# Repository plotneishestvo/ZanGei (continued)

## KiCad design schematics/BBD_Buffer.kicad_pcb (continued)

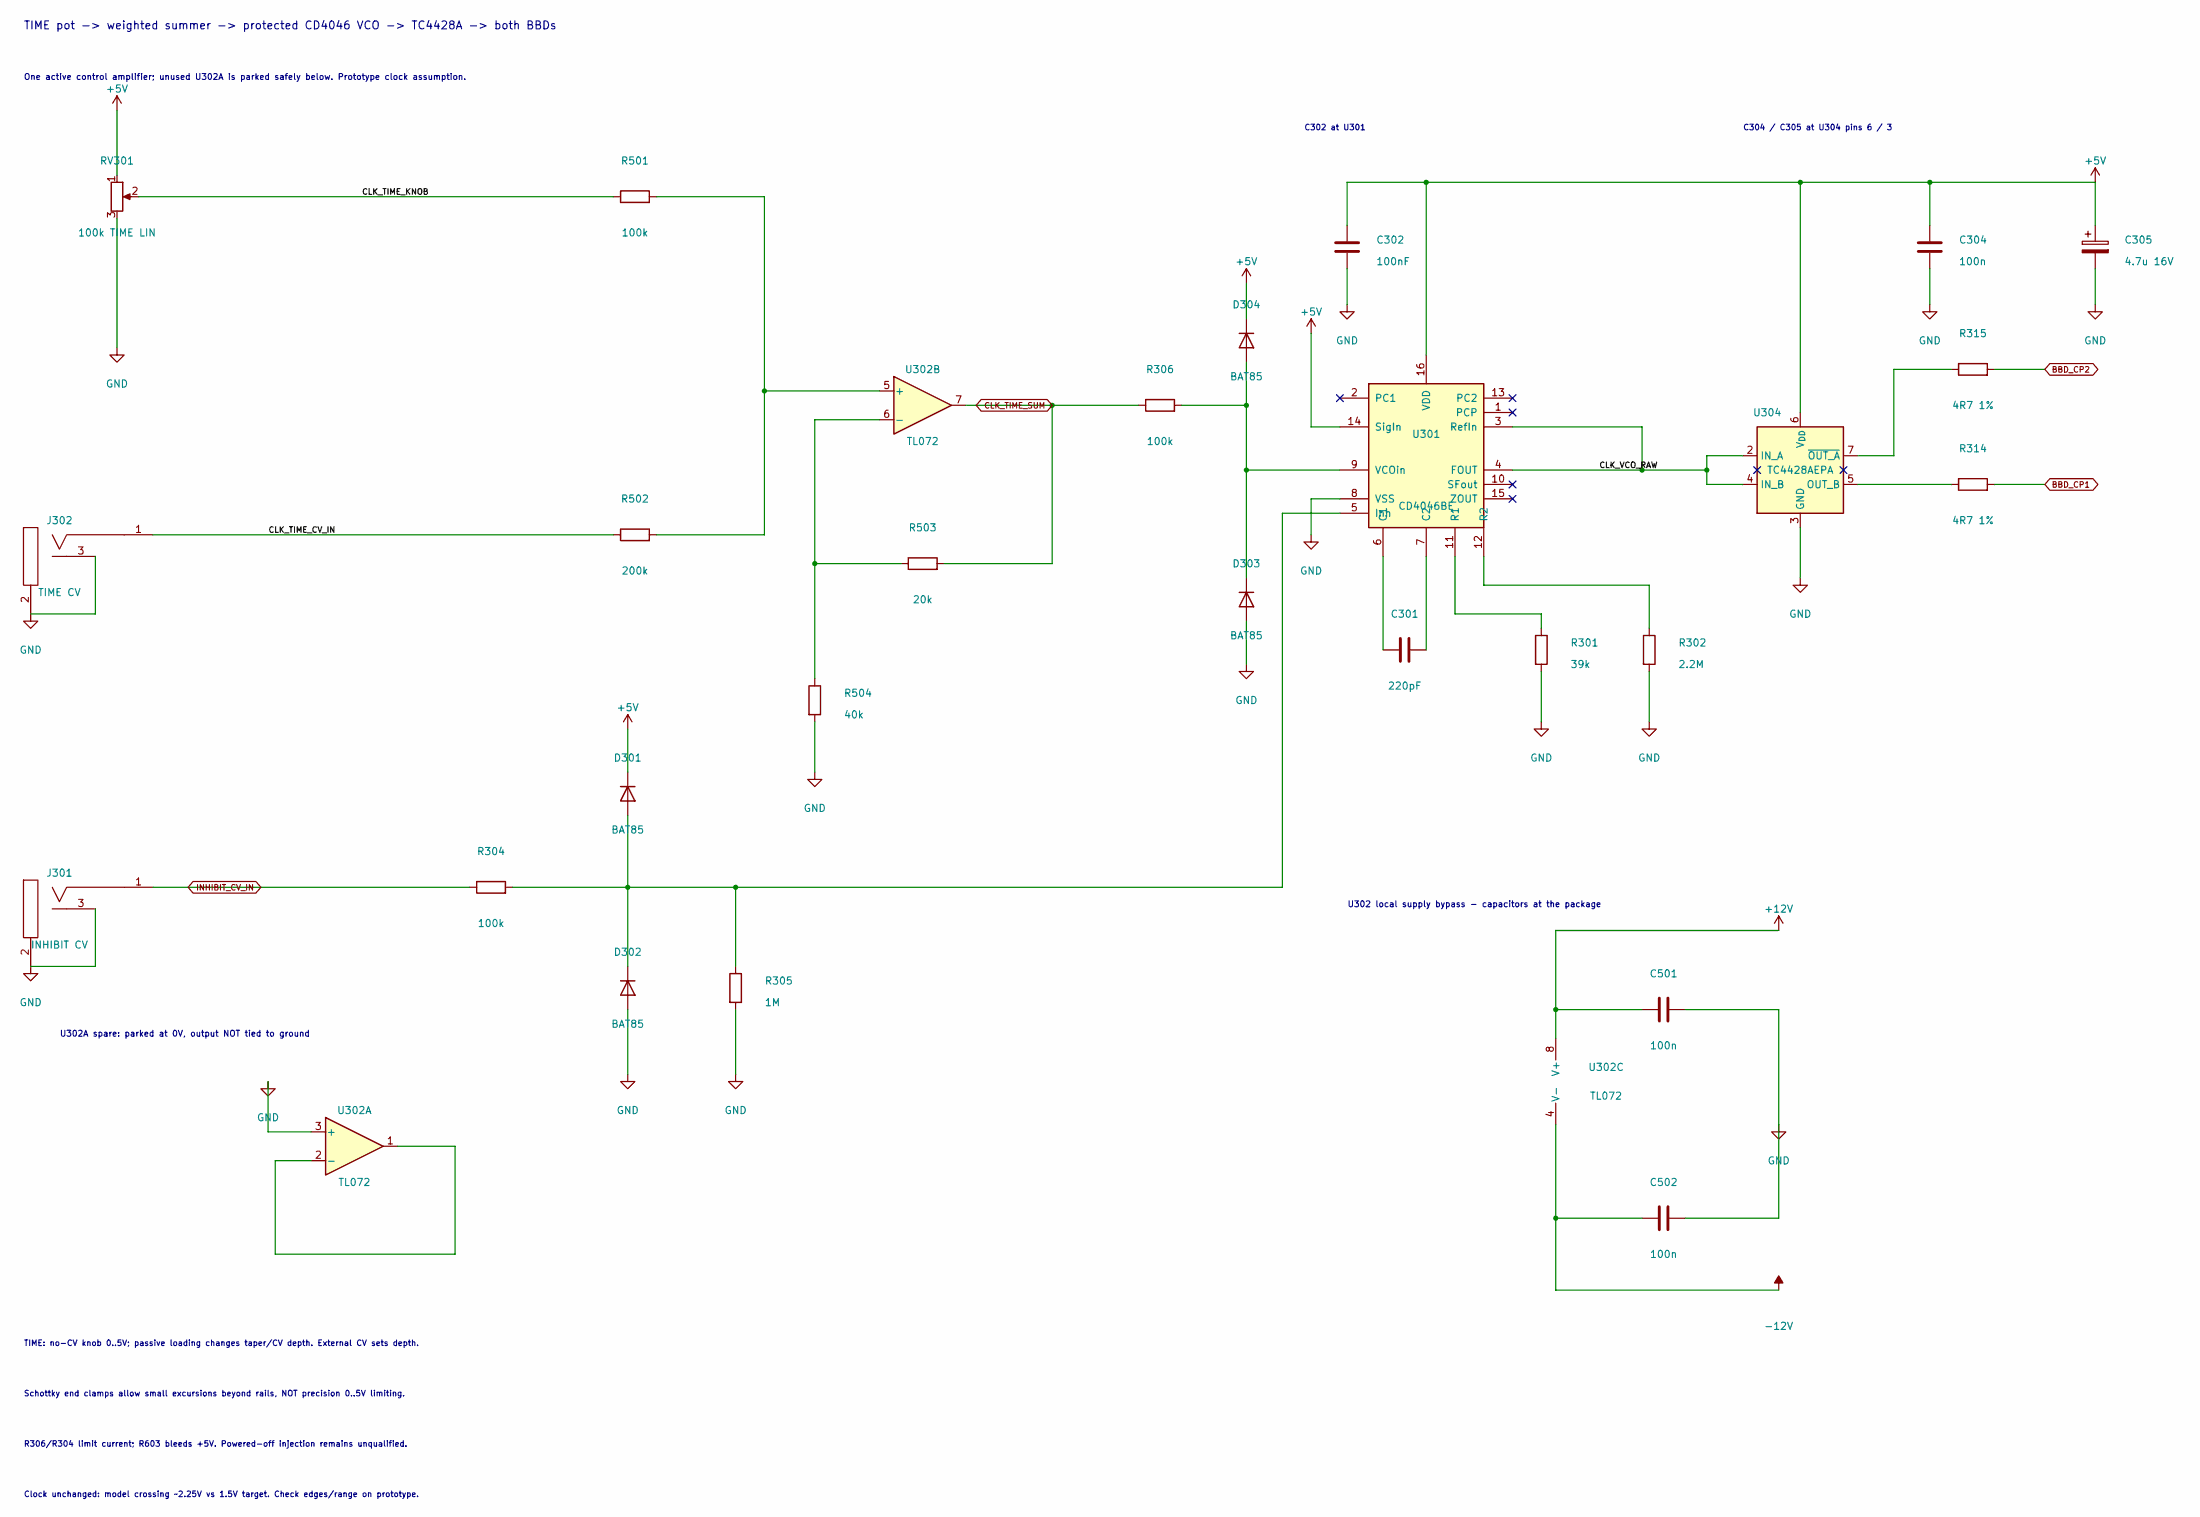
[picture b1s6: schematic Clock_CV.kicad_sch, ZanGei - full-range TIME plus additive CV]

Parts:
C301: 220pF; C_Radial_KEMET_C315_P2.54_Body3.81x5.0
C302: 100nF; C_KEMET_C315C104_P2.54_L3.81_W2.54; MPN C315C104K5R5TA
C304, C501, C502: 100n; C_KEMET_C315C104_P2.54_L3.81_W2.54; MPN C315C104K5R5TA
C305: 4.7u 16V; CP_Radial_D5_H11_P2.00_NoModel
D301, D302, D303, D304: BAT85; D_DO-34_SOD68_P7.62mm_Horizontal
J301: INHIBIT CV; Jack_WQP518MA_PJ398SM_Numeric
J302: TIME CV; Jack_WQP518MA_PJ398SM_Numeric
R301: 39k; R_Axial_L6.8mm_D2.5mm_P10.16mm
R302: 2.2M; R_Axial_L9.25mm_D3.6mm_P12.70mm
R304, R306, R501: 100k; R_Axial_L6.8mm_D2.5mm_P10.16mm
R305: 1M; R_Axial_L6.8mm_D2.5mm_P10.16mm
R314, R315: 4R7 1%; R_Axial_L6.8mm_D2.5mm_P10.16mm
R502: 200k; R_Axial_L6.8mm_D2.5mm_P10.16mm
R503: 20k; R_Axial_L6.8mm_D2.5mm_P10.16mm
R504: 40k; R_Axial_L6.8mm_D2.5mm_P10.16mm
RV301: 100k TIME LIN; Potentiometer_RV09_ExplodingShed_101018
U301: CD4046BE; DIP-16_W7.62mm_Socket
U302: TL072; DIP-8_W7.62mm_Socket
U304: TC4428AEPA; DIP-8_W7.62mm_Socket

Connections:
+5V: C302.1, C304.1, C305.1, D301.1 (K), D304.1 (K), RV301.1, U301.14 (SigIn), U301.16 (VDD), U304.6 (V_{DD}); also elsewhere on the board
+12V: C501.1, U302.8 (V+); also elsewhere on the board
-12V: C502.1, U302.4 (V-); also elsewhere on the board
/Clock and CV/CLK_TIME_CV_IN: J302.1 (SIG), R502.1
/Clock and CV/CLK_TIME_KNOB: R501.1, RV301.2
/Clock and CV/CLK_VCO_RAW: U301.3 (RefIn), U301.4 (FOUT), U304.2 (IN_A), U304.4 (IN_B)
BBD_CP1: R314.2; also elsewhere on the board
BBD_CP2: R315.2; also elsewhere on the board
CLK_TIME_SUM: R306.1, R503.2, U302.7; also elsewhere on the board
GND: C302.2, C304.2, C305.2, C501.2, C502.2, D302.2 (A), D303.2 (A), J301.2 (SHEILD), J301.3 (SW), J302.2 (SHEILD), J302.3 (SW), R301.2, R302.2, R305.2, R504.2, RV301.3, U301.8 (VSS), U302.3 (+), U304.3 (GND); also elsewhere on the board
INHIBIT_CV_IN: J301.1 (SIG), R304.1; also elsewhere on the board
unnamed: D301.2 (A), D302.1 (K), R304.2, R305.1, U301.5 (Inh)
unnamed: D303.1 (K), D304.2 (A), R306.2, U301.9 (VCOin)
unnamed: C301.1, U301.6 (C1)
unnamed: C301.2, U301.7 (C2)
unnamed: R301.1, U301.11 (R1)
unnamed: R302.1, U301.12 (R2)
unnamed: U302.1, U302.2 (-)
unnamed: R501.2, R502.2, U302.5 (+)
unnamed: R503.1, R504.1, U302.6 (-)
unnamed: R314.1, U304.5 (OUT_B)
unnamed: R315.1, U304.7 (~OUT_A)

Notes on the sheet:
Clock unchanged: model crossing ~2.25V vs 1.5V target. Check edges/range on prototype.
U302A spare: parked at 0V, output NOT tied to ground
R306/R304 limit current; R603 bleeds +5V. Powered-off injection remains unqualified.
TIME: no-CV knob 0..5V; passive loading changes taper/CV depth. External CV sets depth.
TIME pot -> weighted summer -> protected CD4046 VCO -> TC4428A -> both BBDs
C304 / C305 at U304 pins 6 / 3
One active control amplifier; unused U302A is parked safely below. Prototype clock assumption.
U302 local supply bypass - capacitors at the package
C302 at U301
Schottky end clamps allow small excursions beyond rails, NOT precision 0..5V limiting.

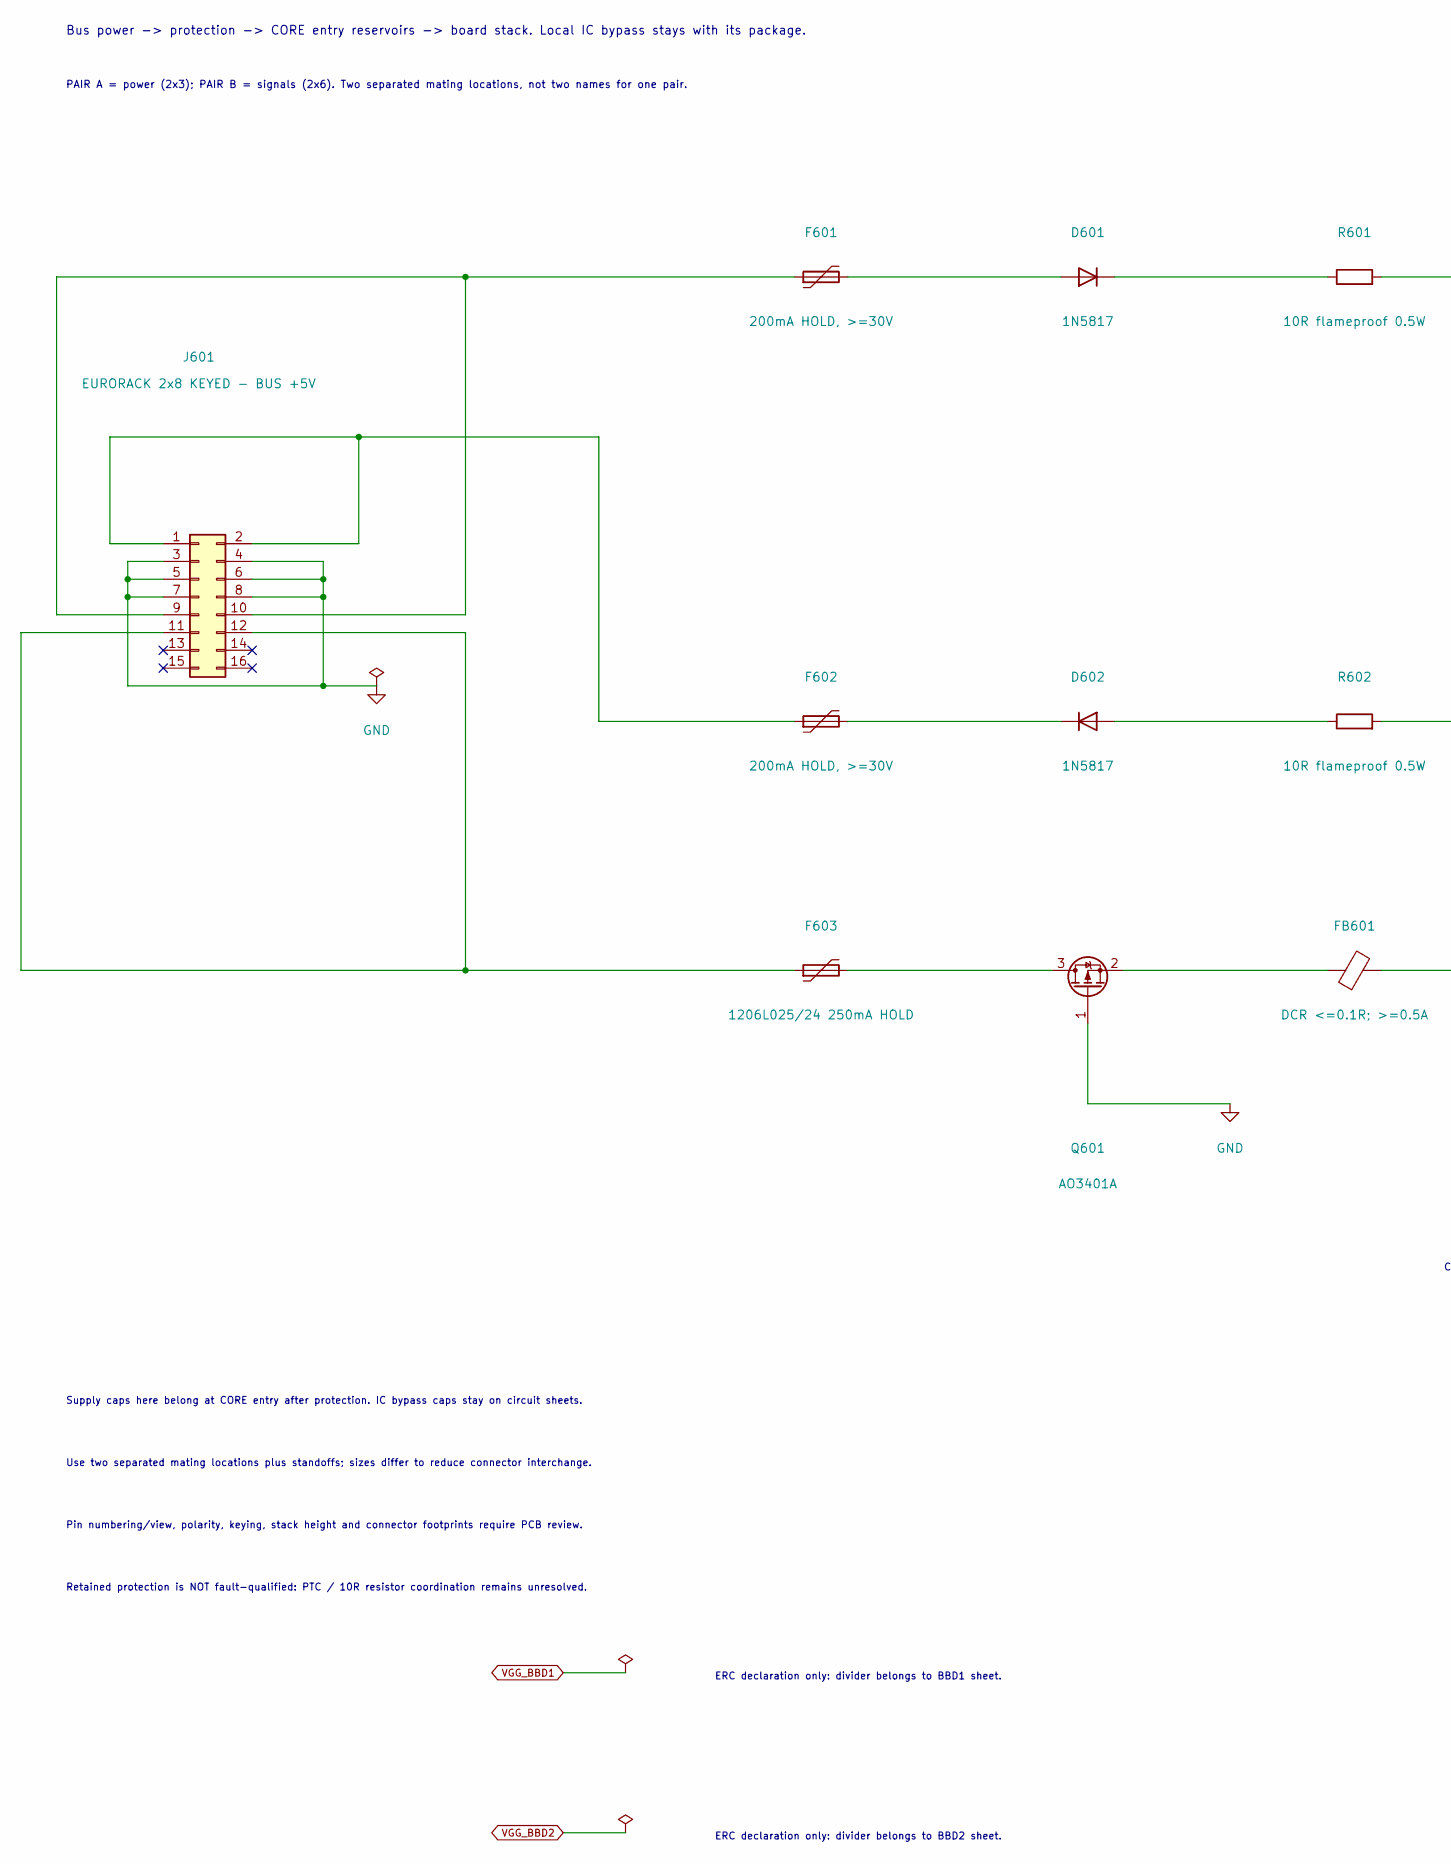
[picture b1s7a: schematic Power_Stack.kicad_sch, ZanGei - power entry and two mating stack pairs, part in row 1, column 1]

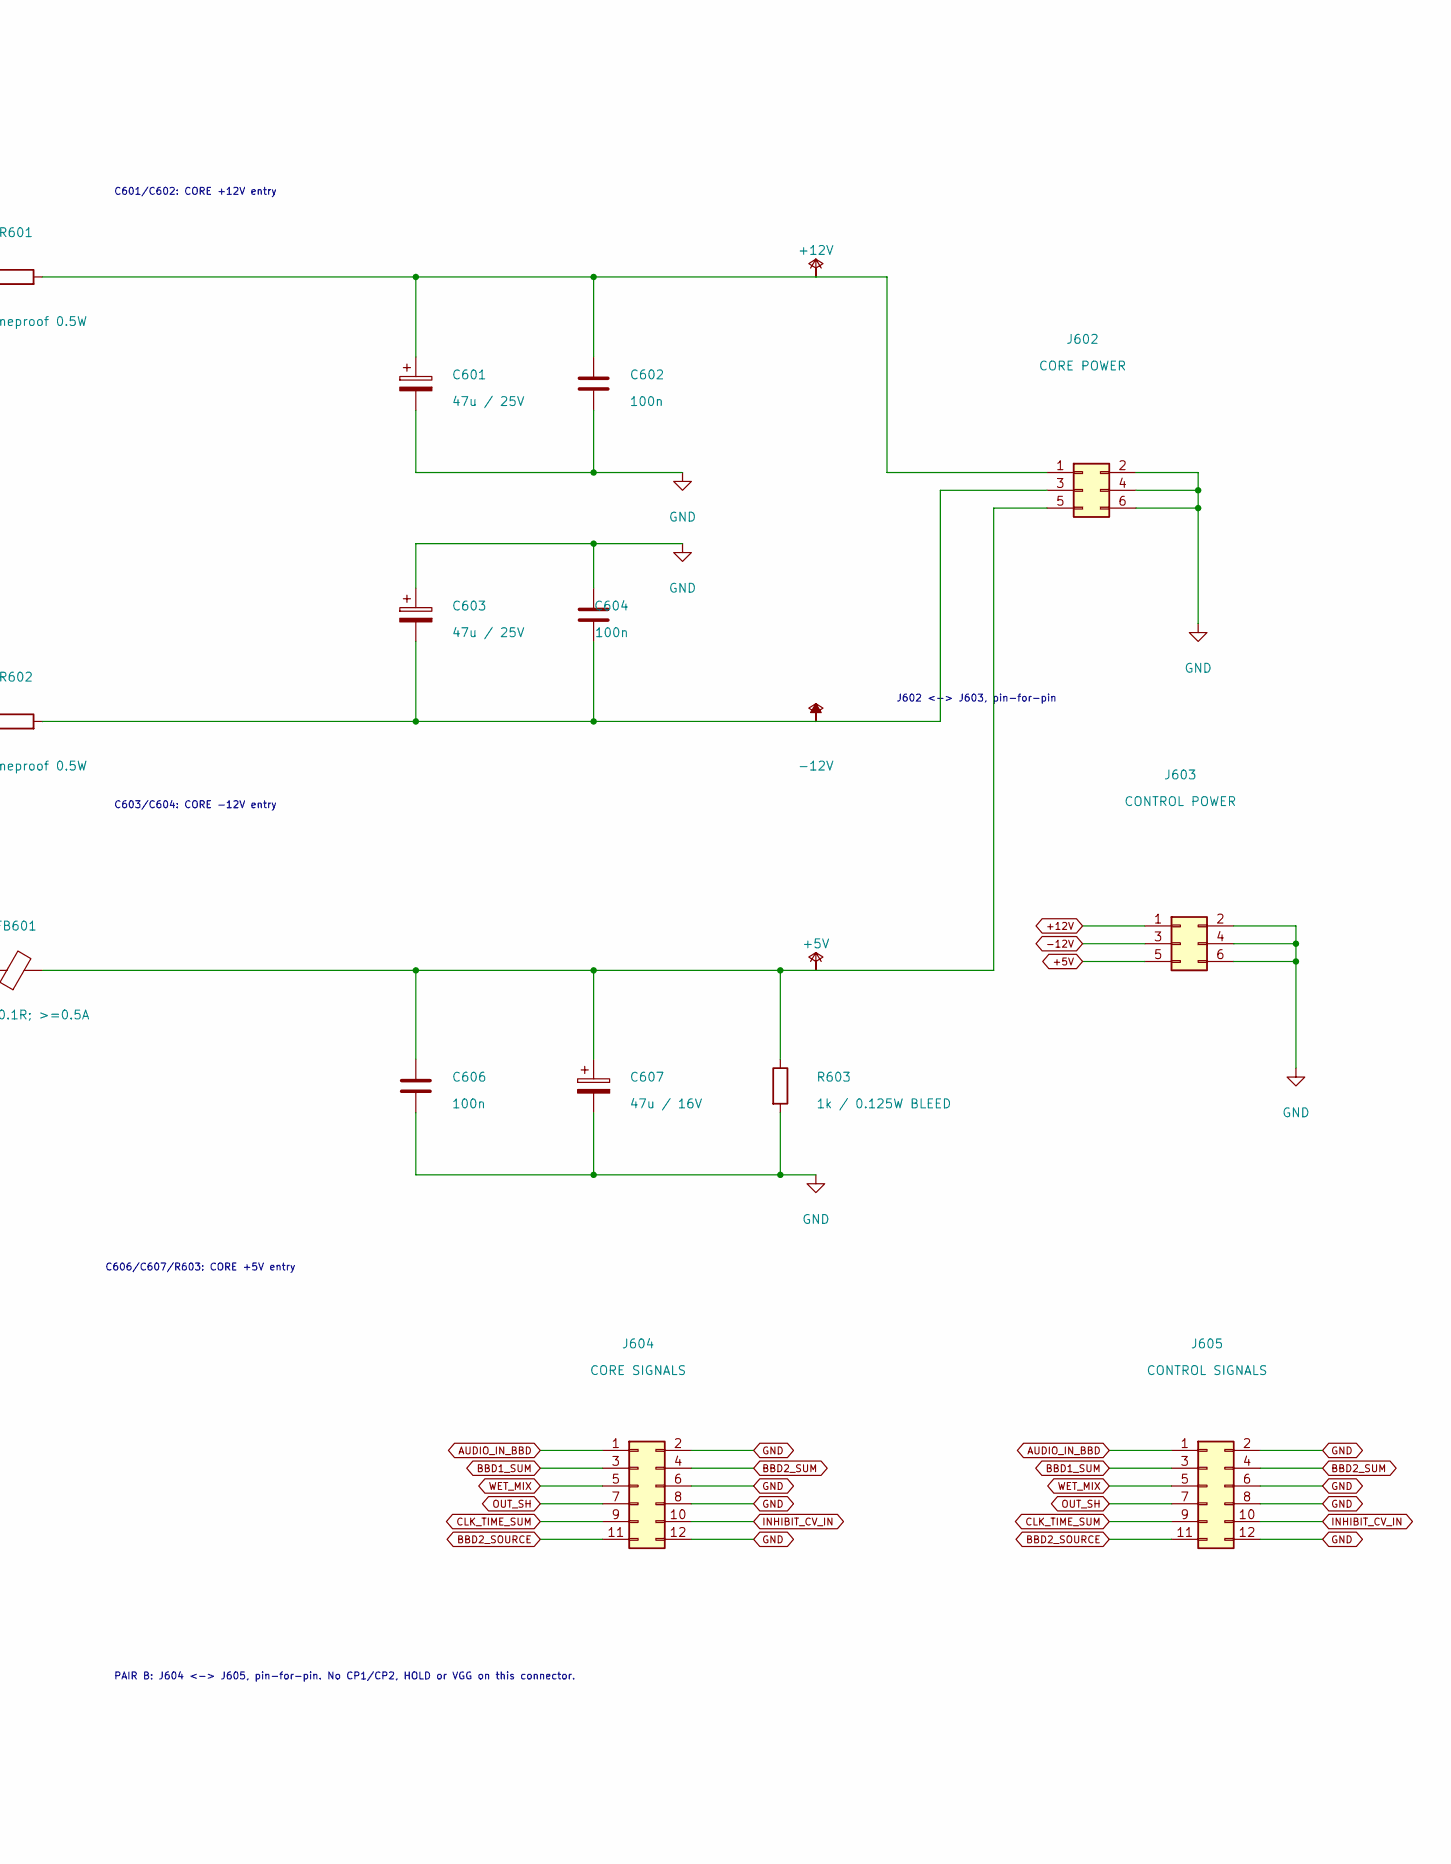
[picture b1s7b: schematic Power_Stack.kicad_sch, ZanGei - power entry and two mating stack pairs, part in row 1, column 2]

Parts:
C601, C603: 47u / 25V; CP_Radial_D6.3mm_P2.50mm
C602, C604, C606: 100n; C_KEMET_C315C104_P2.54_L3.81_W2.54; MPN C315C104K5R5TA
C607: 47u / 16V; CP_Radial_D6.3mm_P2.50mm
D601, D602: 1N5817; D_DO-41_SOD81_P10.16mm_Horizontal
F601, F602: 200mA HOLD, >=30V; PTC_Bourns_MF-R020_P5.10; MPN MF-R020-2
F603: 1206L025/24 250mA HOLD; PTC_Littelfuse_1206L_ManufacturerLands; MPN 1206L025/24YR
FB601: DCR <=0.1R; >=0.5A; Ferrite_Murata_BLM31PG_Pads1.5x1.8_Gap2.0; MPN BLM31PG121SN1L
J601: EURORACK 2x8 KEYED - BUS +5V; IDC-Header_2x08_P2.54mm_Vertical
J602: CORE POWER; PinHeader_2x03_P2.54mm_Vertical
J603: CONTROL POWER; PinSocket_2x03_P2.54mm_Vertical
J604: CORE SIGNALS; PinHeader_2x06_P2.54mm_Vertical
J605: CONTROL SIGNALS; PinSocket_2x06_P2.54mm_Vertical
Q601: AO3401A; SOT-23-3
R601, R602: 10R flameproof 0.5W; R_Axial_L6.8mm_D2.5mm_P10.16mm; MPN NFR25H0001009JR500
R603: 1k / 0.125W BLEED; R_Axial_L6.8mm_D2.5mm_P10.16mm

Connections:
+5V: C606.1, C607.1, FB601.2, J602.5, J603.5, R603.1; also elsewhere on the board
+12V: C601.1, C602.1, J602.1, J603.1, R601.2; also elsewhere on the board
-12V: C603.2, C604.1, J602.3, J603.3, R602.2; also elsewhere on the board
AUDIO_IN_BBD: J604.1, J605.1; also elsewhere on the board
BBD1_SUM: J604.3, J605.3; also elsewhere on the board
BBD2_SOURCE: J604.11, J605.11; also elsewhere on the board
BBD2_SUM: J604.4, J605.4; also elsewhere on the board
CLK_TIME_SUM: J604.9, J605.9; also elsewhere on the board
GND: C601.2, C602.2, C603.1, C604.2, C606.2, C607.2, J601.3, J601.4, J601.5, J601.6, J601.7, J601.8, J602.2, J602.4, J602.6, J603.2, J603.4, J603.6, J604.2, J604.6, J604.8, J604.12, J605.2, J605.6, J605.8, J605.12, Q601.1 (G), R603.2; also elsewhere on the board
INHIBIT_CV_IN: J604.10, J605.10; also elsewhere on the board
unnamed: D601.2 (A), F601.2
unnamed: D601.1 (K), R601.1
unnamed: D602.2 (A), R602.1
unnamed: D602.1 (K), F602.2
unnamed: F602.1, J601.1, J601.2
unnamed: F601.1, J601.9, J601.10
unnamed: F603.1, J601.11, J601.12
unnamed: F603.2, Q601.3 (D)
unnamed: FB601.1, Q601.2 (S)
OUT_SH: J604.7, J605.7; also elsewhere on the board
WET_MIX: J604.5, J605.5; also elsewhere on the board

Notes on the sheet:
Pin numbering/view, polarity, keying, stack height and connector footprints require PCB review.
C606/C607/R603: CORE +5V entry
ERC declaration only: divider belongs to BBD1 sheet.
Supply caps here belong at CORE entry after protection. IC bypass caps stay on circuit sheets.
PAIR B: J604 <-> J605, pin-for-pin. No CP1/CP2, HOLD or VGG on this connector.
PAIR A = power (2x3); PAIR B = signals (2x6). Two separated mating locations, not two names for one pair.
ERC declaration only: divider belongs to BBD2 sheet.
J602 <-> J603, pin-for-pin
Retained protection is NOT fault-qualified: PTC / 10R resistor coordination remains unresolved.
C601/C602: CORE +12V entry
C603/C604: CORE -12V entry
Use two separated mating locations plus standoffs; sizes differ to reduce connector interchange.
Bus power -> protection -> CORE entry reservoirs -> board stack. Local IC bypass stays with its package.

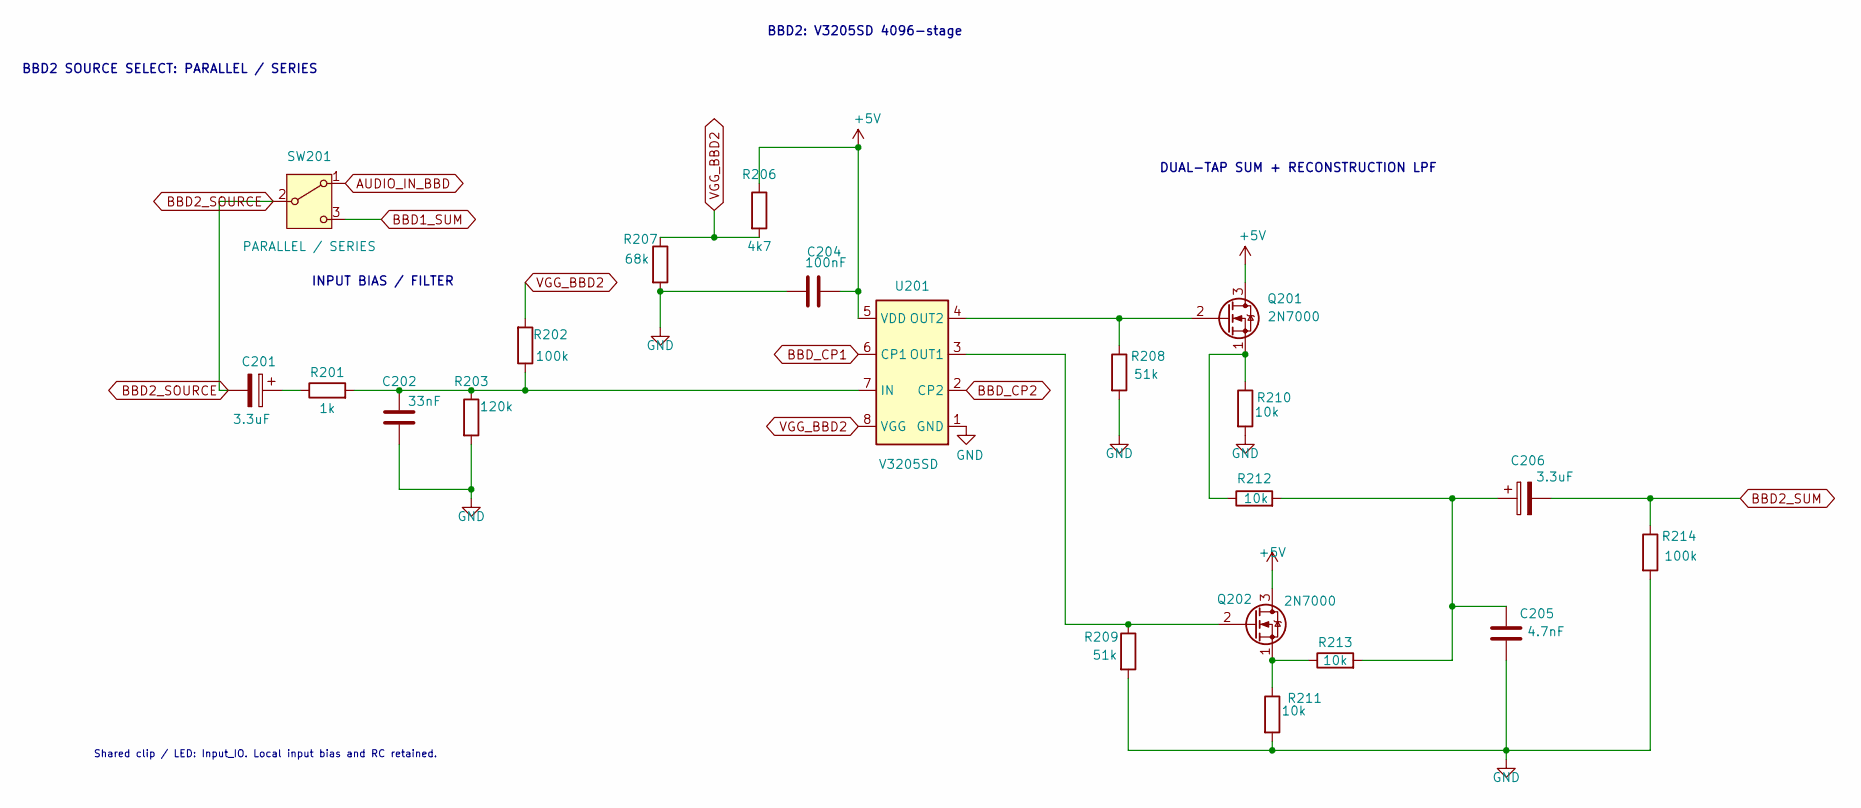
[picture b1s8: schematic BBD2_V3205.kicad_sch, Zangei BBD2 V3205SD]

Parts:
C201, C206: 3.3uF; CP_Radial_D5.0mm_P2.50mm
C202: 33nF; C_Rect_L7.2mm_W2.5mm_P5.00mm
C204: 100nF; C_KEMET_C315C104_P2.54_L3.81_W2.54; MPN C315C104K5R5TA
C205: 4.7nF; C_Rect_L7.2mm_W2.5mm_P5.00mm
Q201, Q202: 2N7000; TO-92_Inline
R201: 1k; R_Axial_L6.8mm_D2.5mm_P10.16mm
R202, R214: 100k; R_Axial_L6.8mm_D2.5mm_P10.16mm
R203: 120k; R_Axial_L6.8mm_D2.5mm_P10.16mm
R206: 4k7; R_Axial_L6.8mm_D2.5mm_P10.16mm
R207: 68k; R_Axial_L6.8mm_D2.5mm_P10.16mm
R208, R209: 51k; R_Axial_L6.8mm_D2.5mm_P10.16mm
R210, R211, R212, R213: 10k; R_Axial_L6.8mm_D2.5mm_P10.16mm
SW201: PARALLEL / SERIES; Switch_Salecom_SKS_SP_Straight
U201: V3205SD; V3205SD_DIP16_Socket_LogicalPads

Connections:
+5V: C204.1, Q201.3 (D), Q202.3 (D), R206.1, U201.5 (VDD); also elsewhere on the board
AUDIO_IN_BBD: SW201.1 (A); also elsewhere on the board
BBD1_SUM: SW201.3 (C); also elsewhere on the board
BBD2_SOURCE: C201.2, SW201.2 (B); also elsewhere on the board
BBD2_SUM: C206.2, R214.1; also elsewhere on the board
BBD_CP1: U201.6 (CP1); also elsewhere on the board
BBD_CP2: U201.2 (CP2); also elsewhere on the board
GND: C202.2, C204.2, C205.2, R203.2, R207.2, R208.2, R209.2, R210.2, R211.2, R214.2, U201.1 (GND); also elsewhere on the board
unnamed: C201.1, R201.1
unnamed: C205.1, C206.1, R212.2, R213.2
unnamed: Q201.2 (G), R208.1, U201.4 (OUT2)
unnamed: Q201.1 (S), R210.1, R212.1
unnamed: Q202.2 (G), R209.1, U201.3 (OUT1)
unnamed: Q202.1 (S), R211.1, R213.1
unnamed: C202.1, R201.2, R202.1, R203.1, U201.7 (IN)
VGG_BBD2: R202.2, R206.2, R207.1, U201.8 (VGG)

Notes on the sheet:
DUAL-TAP SUM + RECONSTRUCTION LPF
Shared clip / LED: Input_IO. Local input bias and RC retained.
BBD2 SOURCE SELECT: PARALLEL / SERIES
INPUT BIAS / FILTER
BBD2: V3205SD 4096-stage

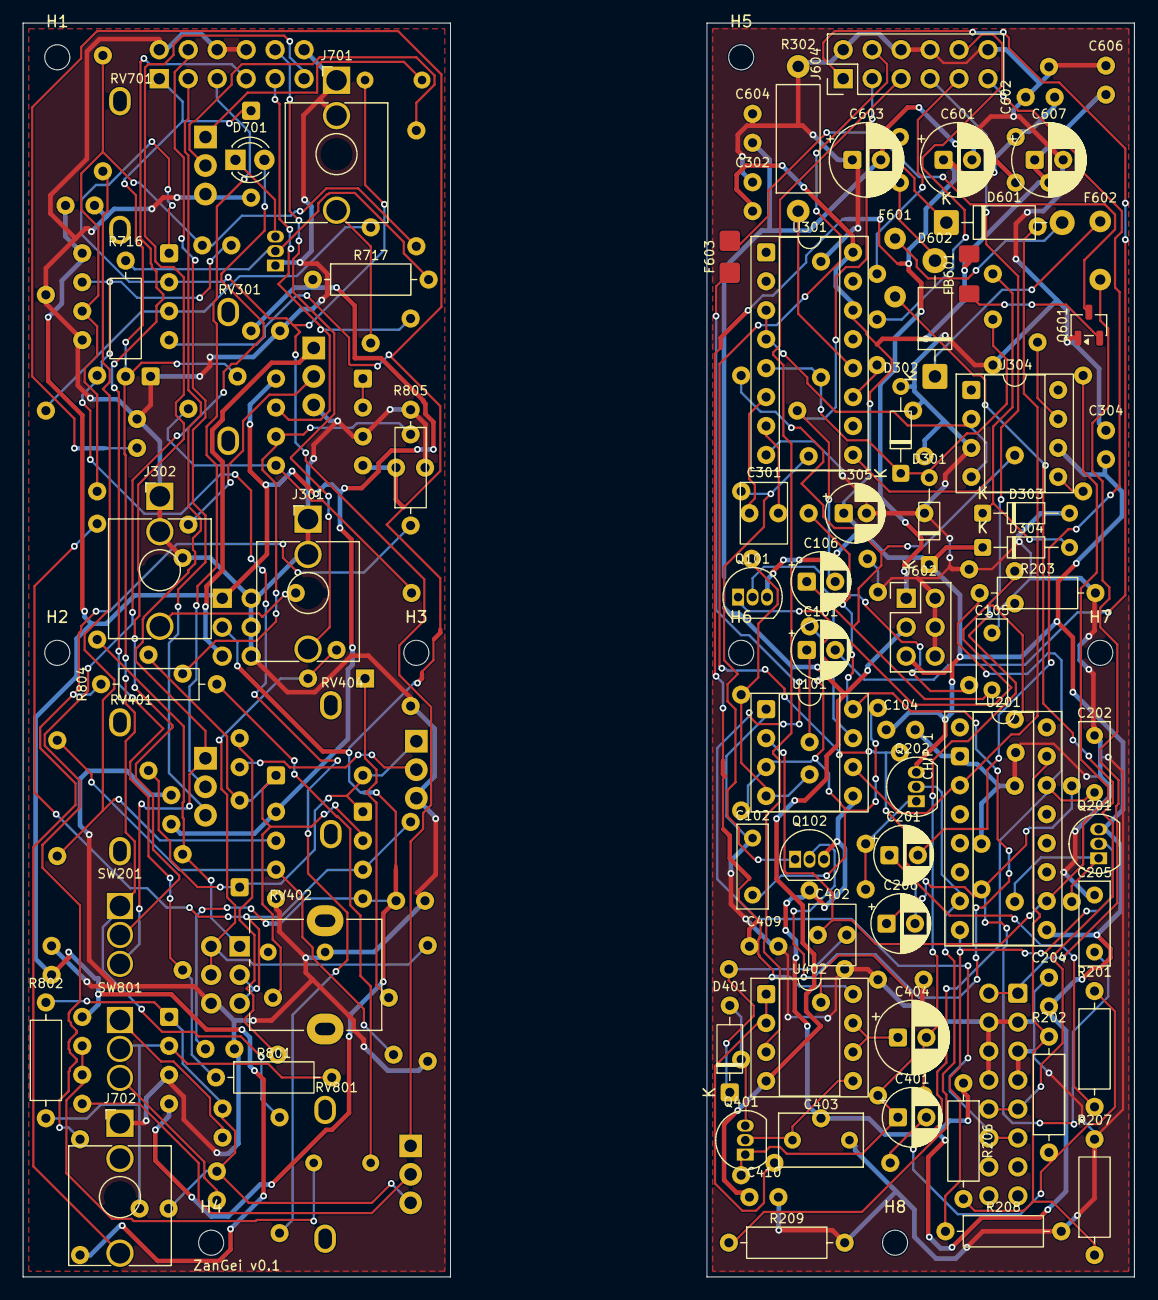
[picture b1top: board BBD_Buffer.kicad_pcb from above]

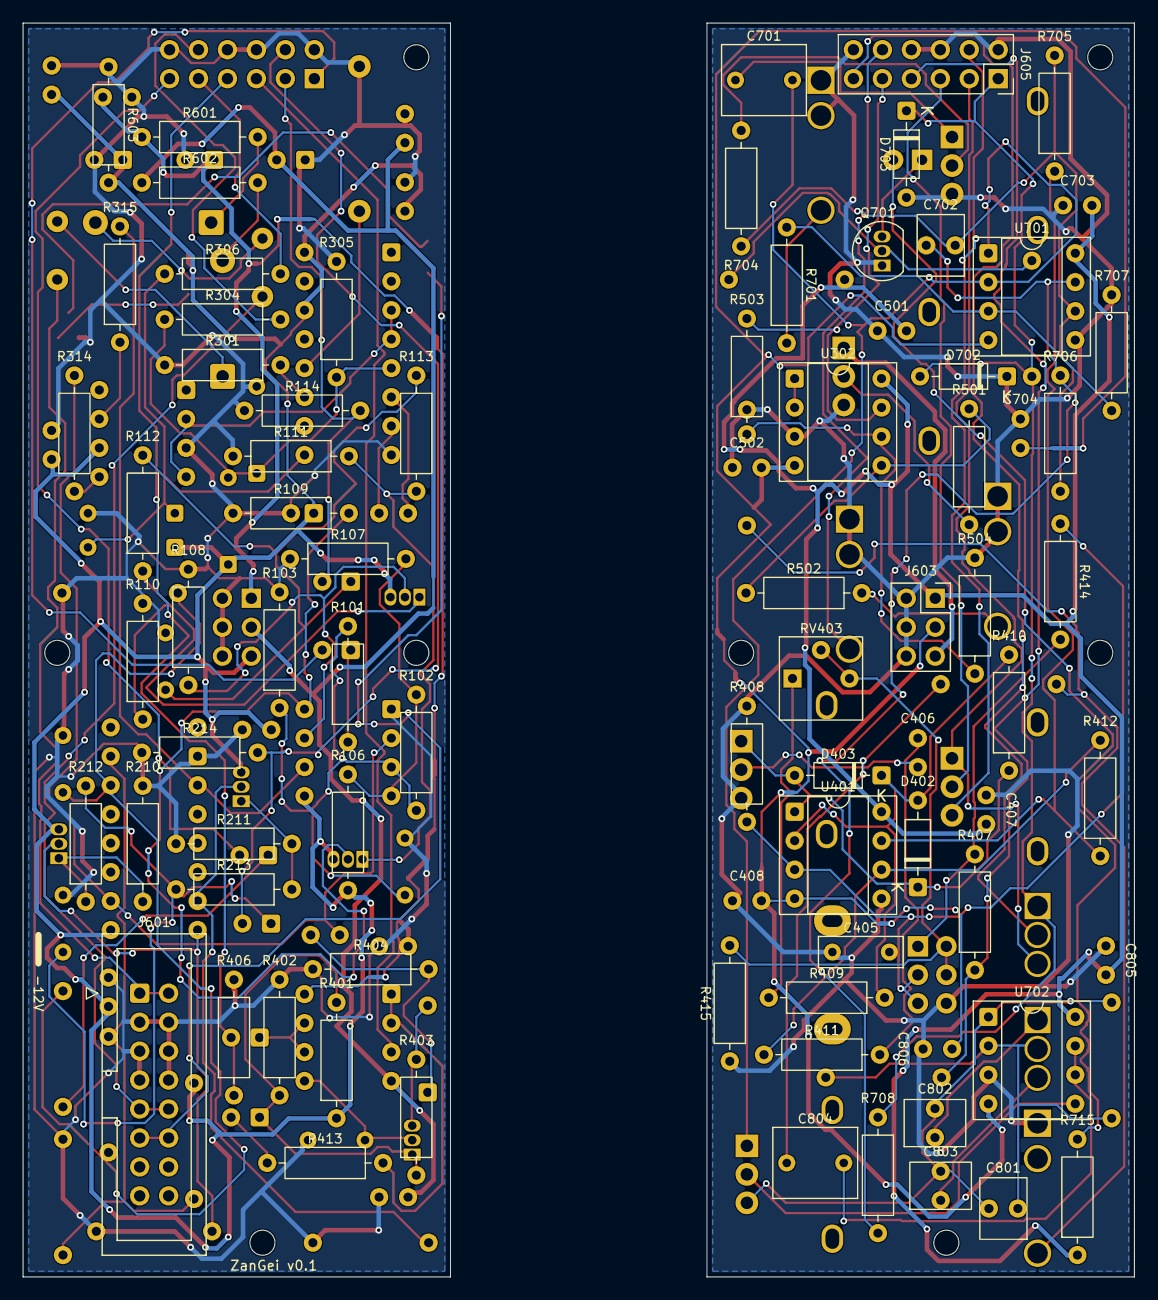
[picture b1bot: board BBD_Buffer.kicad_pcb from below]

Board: 2 copper layers, 97.5 x 110.0 mm, 165 parts (80 on the bottom side), 88 nets.

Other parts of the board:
H1, H2, H3, H4, H5, H6, H7, H8: MountingHole_2.2mm_M2

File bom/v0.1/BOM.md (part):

# ZanGei v0.1 — bill of materials

Quantities are for **one module: 157 schematic components in 64 groups**, plus the separate assembly hardware below. These are fitted quantities, not pack sizes or spare allowances. Supplier links identify the selected parts; availability and physical fit must be checked.

- [Grouped CSV](BOM_GROUPED.csv): quantities, exact schematic values, selected parts and footprints.
- [Per-reference CSV](BOM_PER_REFERENCE.csv): one row per schematic position, with its exact value, footprint and PCB.
- [Build and power precautions](../../docs/BUILD.md), [assembly access](../../schematics/assembly/README.md) and [panel fit](../../mechanical/README.md).

The PCB is mostly through-hole. **Q601 (SOT-23), F603 (1206 PTC) and FB601 (1206 ferrite) are SMD.** U201 V3205SD has a special spaced eight-lead package using a 16-position socket pattern. Do not substitute ordinary DIP8.

## Components

Exact KiCad footprint assignments are in both CSVs. Generic resistors are specified individually by value, tolerance, power and fit; no assortment is required. Exact precision and protection part selections must be retained. R302's source record lacks tolerance/power: verify those rather than assuming a generic resistor specification.


### ICs

| Qty | References | Selected part / specification | Fit / electrical notes |
|---:|---|---|---|
| 1 | U301 | [CD4046BE  CMOS digital Phase-Locked Loop DIL16](https://en.uraltone.com/catalogsearch/result/?q=184-4046BE) | Through-hole DIL16. |
| 1 | U304 | [TC4428AEPA](https://www.digikey.com/en/products/detail/microchip-technol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 | Exact A-version complementary inverting/non-inverting driver; through-hole PDIP8, not SOIC/MSOP. |
| 5 | U302, U401, U402, U701, U702 | [TL072ACP - op amp -Texas instruments](https://en.uraltone.com/catalogsearch/result/?q=184-TL072ACP) | Texas Instruments TL072ACP, DIP8; not an automatic NE5532 substitution. |
| 1 | U201 | [Coolaudio V3205SD special spaced 8-lead BBD](https://www.op-electronics.com/en/delay-chips/95-coolaudio-v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 | Special spaced eight-lead package in selected holes of a 16-position socket pattern; NOT ordinary consecutive-pin DIP8. |
| 1 | U101 | [Coolaudio V3208D 2048-Stage Low-Noise BBD Analog Delay Line IC (DIP8)](https://en.uraltone.com/catalogsearch/result/?q=184S-V3208D) | Coolaudio 2048-stage BBD, DIP8; distinct from U201 V3205SD. |

### Transistors

| Qty | References | Selected part / specification | Fit / electrical notes |
|---:|---|---|---|
| 1 | Q701 | [2N3904BU](https://www.digikey.com/en/products/detail/onsemi/2N3904BU/1413) | onsemi TO-92; verify received pin order against footprint. |
| 1 | Q401 | [2N5457 J-FET N-channel Fairchild NOS USA](https://en.uraltone.com/catalogsearch/result/?q=181-2N5457-FAIR) | Selected Fairchild NOS part: physical pins 1=D, 2=S, 3=G; other manufacturers may differ. |
| 4 | Q101, Q102, Q201, Q202 | [2N7000 Transistor N-MOSFET, 60V, 200mA, TO-92](https://en.uraltone.com/catalogsearch/result/?q=181-2N7000) | 60 V, 200 mA TO-92; verify received pin order. |
| 1 | Q601 | [AO3401A](https://www.digikey.com/en/products/detail/alpha-omega-semic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 | P-channel SOT-23; SMD. |

### Capacitors

| Qty | References | Selected part / specification | Fit / electrical notes |
|---:|---|---|---|
| 1 | C801 | 10 pF — [C315C100J5G5TA](https://www.digikey.com/en/products/detail/kemet/C315C100J5G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 | 10 pF C0G, 5%, 50 V; P2.54 mm. |
| 1 | C405 | 10 nF — [R82EC2100AA50J](https://www.digikey.com/en/products/detail/kemet/R82EC2100AA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 | 10 nF polyester film, 5%, 100 V; P5 mm; nominal body 7.2 x 2.5 mm. |
| 18 | C104, C204, C302, C304, C406, C407, C408, C409, C410, C501, C502, C602, C604, C606, C703, C704, C805, C806 | 100 nF — [C315C104K5R5TA](https://www.digikey.com/en/products/detail/kemet/C315C104K5R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 | 100 nF X7R, 50 V; compact P2.54 mm body required. |
| 2 | C701, C804 | 1 uF — [R82EC4100AA70J](https://www.digikey.com/en/products/detail/kemet/R82EC4100AA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 | 1 uF polyester film, 5%, 100 V; P5 mm; nominal body 7.2 x 6 mm, seated height 11.1 mm. Do not substitute ceramic. |
| 1 | C403 | [KEMET 15nF (0.015uF) / 400V polyester film capacitor, radial](https://en.uraltone.com/catalogsearch/result/?q=545-MC5-15N/400V) | 15 nF / 400 V polyester film, radial; check actual body and lead seating. |
| 3 | C301, C402, C803 | 220 pF — [C315C221J5G5TA](https://www.digikey.com/en/products/detail/kemet/C315C221J5G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 | 220 pF C0G, 5%, 50 V; P2.54 mm. |
| 2 | C102, C202 | 33 nF — [R82EC2330AA50J](https://www.digikey.com/en/products/detail/kemet/R82EC2330AA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 | 33 nF polyester film, 5%, 100 V; P5 mm; nominal body 7.2 x 2.5 mm. |
| 5 | C101, C106, C201, C206, C401 | [Nichicon 3.3uF / 50V FW audio electrolytic capacitor, radial](https://en.uraltone.com/catalogsearch/result/?q=518-003-1H5X11UFW) | 3.3 uF / 50 V Nichicon FW; nominal D5 x H11 mm, P2.5 mm; polarised. |
| 1 | C702 | 47 pF — [C315C470J5G5TA](https://www.digikey.com/en/products/detail/kemet/C315C470J5G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 | 47 pF C0G, 5%, 50 V; P2.54 mm. |
| 2 | C105, C205 | 4.7 nF — [R82EC1470AA50J](https://www.digikey.com/en/products/detail/kemet/R82EC1470AA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 | 4.7 nF polyester film, 5%, 100 V; P5 mm; nominal body 7.2 x 2.5 mm. |
| 1 | C305 | [Panasonic 4.7uF 50V 5x11mm; UralTone518-P-4.7-50](https://en.uraltone.com/4-7uf-50v-panasonic-5x11mm-electroly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 | 4.7 uF / 50 V Panasonic; nominal D5 x H11 mm, P2.0 mm; polarised. |
| 4 | C404, C601, C603, C607 | [Nichicon 47uF / 50V electrolytic capacitor, radial](https://en.uraltone.com/catalogsearch/result/?q=518-047-1H6X11UFW) | 47 uF / 50 V Nichicon FW; nominal D6.3 x H11 mm, P2.5 mm; polarised. |
| 1 | C802 | 68 pF — [C315C680J5G5TA](https://www.digikey.com/en/products/detail/kemet/C315C680J5G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 | 68 pF C0G, 5%, 50 V; P2.54 mm. |

### Resistors

| Qty | References | Selected part / specification | Fit / electrical notes |
|---:|---|---|---|
| 2 | R413, R708 | 100 ohm metal-film 0.25W <=1%, axial | Axial metal-film, 0.25 W, <=1%; body <=6.8 x 2.5 mm; form leads to P10.16 mm. |
| 6 | R101, R201, R603, R701, R716, R804 | 1000 ohm metal-film 0.25W <=1%, axial | Axial metal-film, 0.25 W, <=1%; body <=6.8 x 2.5 mm; form leads to P10.16 mm. |
| 9 | R110, R111, R112, R113, R210, R211, R212, R213, R715 | 10000 ohm metal-film 0.25W <=1%, axial | Axial metal-film, 0.25 W, <=1%; body <=6.8 x 2.5 mm; form leads to P10.16 mm. |
| 14 | R102, R114, R202, R214, R304, R306, R401, R402, R403, R406, R411, R501, R705, R805 | 100 kohm — [MFR-25FBF52-100K](https://www.digikey.com/en/products/detail/yageo/MFR-25FBF52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 | Exact 100000 ohm, 1%; axial P10.16 mm. Preserve selected part and verify its rated power/body against manufacturer data. |
| 4 | R305, R408, R704, R707 | 1000000 ohm metal-film 0.25W <=1%, axial | Axial metal-film, 0.25 W, <=1%; body <=6.8 x 2.5 mm; form leads to P10.16 mm. |
| 1 | R407 | 1.2 kohm — [MFR-25FTE52-1K2](https://www.digikey.com/en/products/detail/yageo/MFR-25FTE52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 | Exact 1200 ohm, 1%; axial P10.16 mm. Preserve selected part and verify its rated power/body against manufacturer data. |
| 2 | R103, R203 | 120 kohm — [MFR-25FBF52-120K](https://www.digikey.com/en/products/detail/yageo/MFR-25FBF52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 | Exact 120000 ohm, 1%; axial P10.16 mm. Preserve selected part and verify its rated power/body against manufacturer data. |
| 2 | R503, R801 | 20000 ohm metal-film 0.25W <=1%, axial | Axial metal-film, 0.25 W, <=1%; body <=6.8 x 2.5 mm; form leads to P10.16 mm. |
| 1 | R502 | 200 kohm — [MFR-25FBF52-200K](https://www.digikey.com/en/products/detail/yageo/MFR-25FBF52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 | Exact 200000 ohm, 1%; axial P10.16 mm. Preserve selected part and verify its rated power/body against manufacturer data. |
| 1 | R409 | 2200 ohm metal-film 0.25W <=1%, axial | Axial metal-film, 0.25 W, <=1%; body <=6.8 x 2.5 mm; form leads to P10.16 mm. |
| 1 | R410 | 22 kohm — [MFR-25FBF52-22K](https://www.digikey.com/en/products/detail/yageo/MFR-25FBF52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 | Exact 22000 ohm, 1%; axial P10.16 mm. Preserve selected part and verify its rated power/body against manufacturer data. |
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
